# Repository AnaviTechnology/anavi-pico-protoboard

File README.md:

# ANAVI Pico Protoboard

ANAVI Pico Protoboard is a simple prototyping board for Raspberry Pi Pico. Based on a Raspberry Pi Pico footprint for KiCad by Nicolò Carandini:
https://github.com/ncarandini/KiCad-RP-Pico

# License

The project is released under the [Creative Commons Attribution-ShareAlike 4.0 International (CC BY-SA 4.0)](https://creativecommons.org/licenses/by-sa/4.0/).

Note: This is a human-readable summary of (and not a substitute for) the [license](https://creativecommons.org/licenses/by-sa/4.0/legalcode).

You are free to:

Share — copy and redistribute the material in any medium or format Adapt — remix, transform, and build upon the material for any purpose, even commercially. The licensor cannot revoke these freedoms as long as you follow the license terms. Under the following terms:

Attribution — You must give appropriate credit, provide a link to the license, and indicate if changes were made. You may do so in any reasonable manner, but not in any way that suggests the licensor endorses you or your use. ShareAlike — If you remix, transform, or build upon the material, you must distribute your contributions under the same license as the original. No additional restrictions — You may not apply legal terms or technological measures that legally restrict others from doing anything the license permits. Notices:

You do not have to comply with the license for elements of the material in the public domain or where your use is permitted by an applicable exception or limitation. No warranties are given. The license may not give you all of the permissions necessary for your intended use. For example, other rights such as publicity, privacy, or moral rights may limit how you use the material.

You will have to provide a link to the original creator of the project http://www.anavi.technology on any documentation or website.

Credit can be attributed through a link to the creator website: http://www.anavi.technology

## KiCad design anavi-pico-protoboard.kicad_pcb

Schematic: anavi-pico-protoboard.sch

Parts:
J1, J2: Conn_01x20; PinSocket_1x20_P1.00mm_Vertical
J3: Conn_01x03; PinSocket_1x03_P1.00mm_Vertical
J4, J5: Conn_01x03_Male; PinHeader_1x03_P2.54mm_Vertical
U1: Pico; RPi_Pico_SMD_TH

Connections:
GND: J1.3, J1.8, J1.13, J1.18, J2.3, J2.13, J2.18, J3.2, J4.1, J4.2, J4.3, J5.1, J5.2, J5.3, U1.3, U1.8, U1.13, U1.18, U1.23, U1.28, U1.38, U1.42
unnamed: J1.1, U1.1
unnamed: J1.2, U1.2
unnamed: J1.4, U1.4
unnamed: J1.5, U1.5
unnamed: J1.6, U1.6
unnamed: J1.7, U1.7
unnamed: J1.9, U1.9
unnamed: J1.10, U1.10
unnamed: J1.11, U1.11
unnamed: J1.12, U1.12
unnamed: J1.14, U1.14
unnamed: J1.15, U1.15
unnamed: J1.16, U1.16
unnamed: J1.17, U1.17
unnamed: J1.19, U1.19
unnamed: J1.20, U1.20
unnamed: J2.1, U1.40
unnamed: J2.2, U1.39
unnamed: J2.4, U1.37
unnamed: J2.5, U1.36
unnamed: J2.6, U1.35
unnamed: J2.7, U1.34
unnamed: J2.8, U1.33
unnamed: J2.9, U1.32
unnamed: J2.10, U1.31
unnamed: J2.11, U1.30
unnamed: J2.12, U1.29
unnamed: J2.14, U1.27
unnamed: J2.15, U1.26
unnamed: J2.16, U1.25
unnamed: J2.17, U1.24
unnamed: J2.19, U1.22
unnamed: J2.20, U1.21
unnamed: J3.1, U1.43
unnamed: J3.3, U1.41

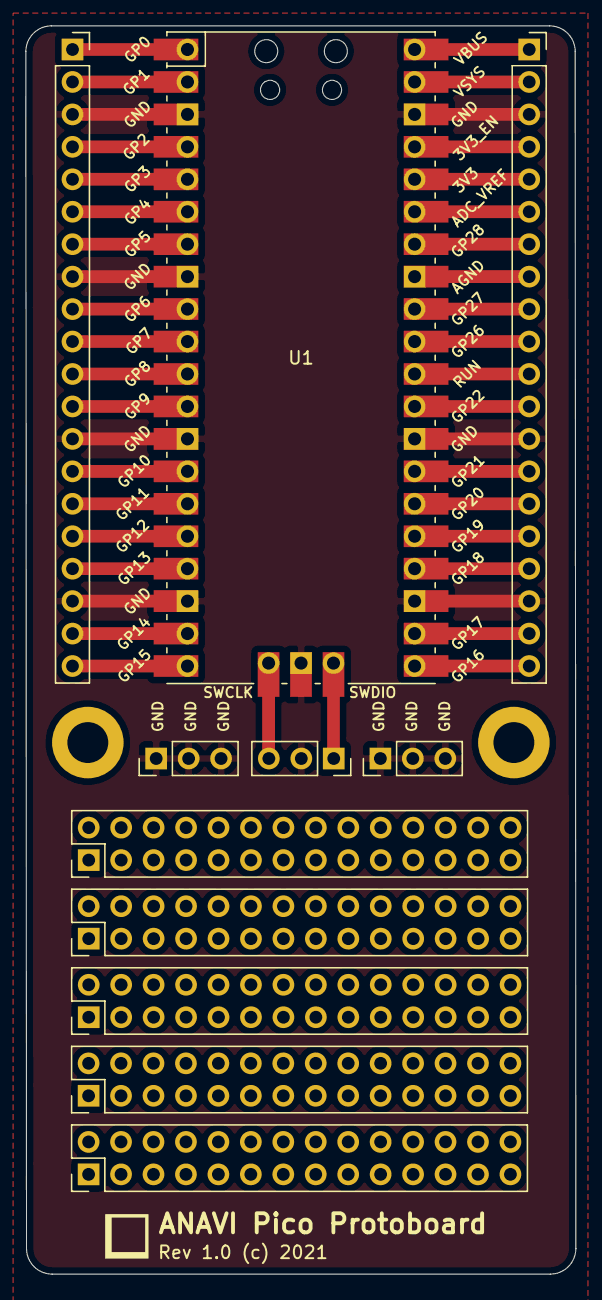
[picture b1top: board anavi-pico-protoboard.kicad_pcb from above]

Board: 2 copper layers, 43.0 x 97.7 mm, 6 parts (0 on the bottom side), 36 nets.

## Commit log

2021-11-04 Initial commit
    Simple prototyping board for Raspberry Pi Pico designed in KiCad.

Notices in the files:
anavi-pico-protoboard.kicad_pcb:
Rev 1.0 (c) 2021
